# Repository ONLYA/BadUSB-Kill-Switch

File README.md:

# BadUSB Kill Switch
Methods to kill BadUSB:
* Software prevention
* Hardware prevention

## Software
This method detects unexpected HID devices input and block all keyboard inputs when that happens. For detail please have a look at [**Software section**](/Software).

## Hardware
This method detects whether the plugged USB device is HID device or not. For details please have a look at [**Hardware section**](/Hardware).

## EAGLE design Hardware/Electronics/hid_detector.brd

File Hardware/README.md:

# Hardware for BadUSB Kill Switch

This uses ATSAMD21E17D as the main chip for detection. This device is powered via the USB *Male* port to computer. When a USB device is plugged into the USB *Female* port on this device, it will start to detect whether the USB device is HID device or not.
* If the inserted USB device is NOT recognised as an HID, the **green** light will be lit and the data paths of it are switched on.
* If the inserted USB device is recognised as an HID, the **red** light will be lit while the **green** light is off and the datapaths of it will be switched off.

This device will keep detecting the USB protocol during the whole insertion in order to prevent possible remote or delayed attacks.

## Electronics [(Folder)](/Hardware/Electronics)
It contains the PCB and circuit design files of this device including the BOM file in csv format. Now it is completed.

## firmware [(Folder)](/Hardware/firmware)
It contains the firmware of the device so that it will work as described above. Now it is NOT completed.

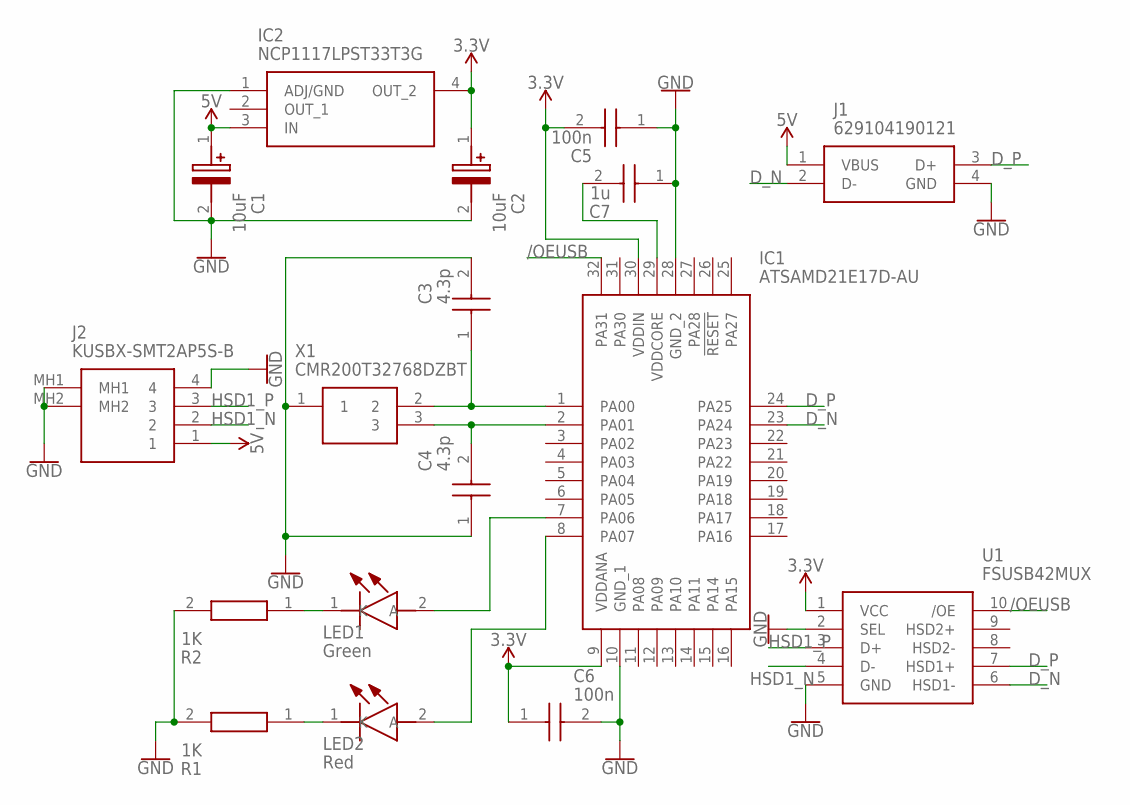
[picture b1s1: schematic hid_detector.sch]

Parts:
C1, C2: 10uF; CAPAE400X550N
C3, C4: 4.3p; CAPC0603X33N
C5, C6: 100n; CAPC1005X55N
C7: 1u; CAPC1005X55N
IC1: ATSAMD21E17D-AU; QFP80P900X900X120-32N
IC2: NCP1117LPST33T3G; SOT230P700X180-4N
J1: 629104190121
J2: KUSBX-SMT2AP5S-B; KUSBXSMT2AP5SB
LED1: Green; LEDC3215X130N
LED2: Red; LEDC1608X85N
R1, R2: 1K; RESC1005X40N
U1: FSUSB42MUX; SOP50P490X110-10N
X1: CMR200T32768DZBT; CMR200T

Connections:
3.3V: C2.1 (+), C5.2, C6.1, IC1.9 (VDDANA), IC1.30 (VDDIN), IC2.4 (OUT_2), U1.1 (VCC)
5V: C1.1 (+), IC2.3 (IN), J1.1 (VBUS), J2.1
/OEUSB: IC1.32 (PA31), U1.10 (/OE)
D_N: IC1.23 (PA24), J1.2 (D-), U1.6 (HSD1-)
D_P: IC1.24 (PA25), J1.3 (D+), U1.7 (HSD1+)
GND: C1.2 (-), C2.2 (-), C3.2, C4.1, C5.1, C6.2, C7.1, IC1.10 (GND_1), IC1.28 (GND_2), IC2.1 (ADJ/GND), J1.4 (GND), J2.4, J2.MH1, J2.MH2, R1.2, R2.2, U1.2 (SEL), U1.5 (GND), X1.1
HSD1_N: J2.2, U1.4 (D-)
HSD1_P: J2.3, U1.3 (D+)
unnamed: C3.1, IC1.1 (PA00), X1.2
unnamed: C4.2, IC1.2 (PA01), X1.3
unnamed: IC1.7 (PA06), LED1.2 (A)
unnamed: LED1.1 (K), R2.1
unnamed: C7.2, IC1.29 (VDDCORE)
unnamed: LED2.1 (K), R1.1
unnamed: IC1.8 (PA07), LED2.2 (A)

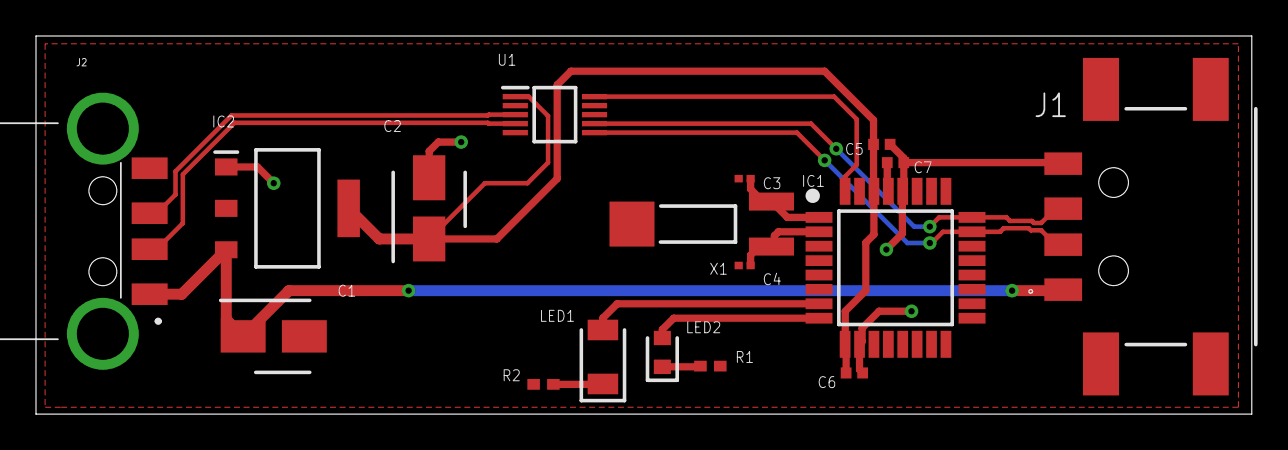
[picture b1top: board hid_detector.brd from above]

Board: 2 copper layers, 67.5 x 21.0 mm, 17 parts (0 on the bottom side), 15 nets.

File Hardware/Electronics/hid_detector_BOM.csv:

"Part";"Value";"Device";"Package";"Description";"DESCRIPTION";"HEIGHT";"MANUFACTURER_NAME";"MANUFACTURER_PART_NUMBER";"MOUSER_PART_NUMBER";"MOUSER_PRICE-STOCK";
"C1";"10uF";"865080440002";"CAPAE400X550N";"Wurth Elektronik 10uF 25 V dc Aluminium Electrolytic Capacitor, WCAP-ASLI Series 2000h 4 (Dia.) x 5.35mm";"Wurth Elektronik 10uF 25 V dc Aluminium Electrolytic Capacitor, WCAP-ASLI Series 2000h 4 (Dia.) x 5.35mm";"5.5mm";"Wurth Elektronik";"865080440002";"710-865080440002";"https://www.mouser.co.uk/ProductDetail/Wurth-Elektronik/8650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";
"C2";"10uF";"865080440002";"CAPAE400X550N";"Wurth Elektronik 10uF 25 V dc Aluminium Electrolytic Capacitor, WCAP-ASLI Series 2000h 4 (Dia.) x 5.35mm";"Wurth Elektronik 10uF 25 V dc Aluminium Electrolytic Capacitor, WCAP-ASLI Series 2000h 4 (Dia.) x 5.35mm";"5.5mm";"Wurth Elektronik";"865080440002";"710-865080440002";"https://www.mouser.co.uk/ProductDetail/Wurth-Elektronik/8650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";
"C3";"4.3p";"GRM0335C1E4R3WA01D";"CAPC0603X33N";"Chip Capacitor value 4R3";"Chip Capacitor value 4R3";"0.33mm";"Murata Electronics";"GRM0335C1E4R3WA01D";"";"";
"C4";"4.3p";"GRM0335C1E4R3WA01D";"CAPC0603X33N";"Chip Capacitor value 4R3";"Chip Capacitor value 4R3";"0.33mm";"Murata Electronics";"GRM0335C1E4R3WA01D";"";"";
"C5";"100n";"EMF105B7104MVHF";"CAPC1005X55N";"Multilayer Ceramic Capacitors MLCC - SMD/SMT 0402 16V 0.1uF 20% AEC-Q200";"Multilayer Ceramic Capacitors MLCC - SMD/SMT 0402 16V 0.1uF 20% AEC-Q200";"0.55mm";"TAIYO YUDEN";"EMF105B7104MVHF";"963-EMF105B7104MVHF";"https://www.mouser.co.uk/ProductDetail/Taiyo-Yuden/EMF105B71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";
"C6";"100n";"EMF105B7104MVHF";"CAPC1005X55N";"Multilayer Ceramic Capacitors MLCC - SMD/SMT 0402 16V 0.1uF 20% AEC-Q200";"Multilayer Ceramic Capacitors MLCC - SMD/SMT 0402 16V 0.1uF 20% AEC-Q200";"0.55mm";"TAIYO YUDEN";"EMF105B7104MVHF";"963-EMF105B7104MVHF";"https://www.mouser.co.uk/ProductDetail/Taiyo-Yuden/EMF105B71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";
"C7";"1u";"EMK105BJ105MVHF";"CAPC1005X55N";"TAIYO YUDEN - EMK105BJ105MVHF - CAPACITOR, MLCC, 0402, 16V ,X5R,Q200 02AH5330";"TAIYO YUDEN - EMK105BJ105MVHF - CAPACITOR, MLCC, 0402, 16V ,X5R,Q200 02AH5330";"0.55mm";"TAIYO YUDEN";"EMK105BJ105MVHF";"963-EMK105BJ105MVHF";"https://www.mouser.co.uk/ProductDetail/Taiyo-Yuden/EMK105BJ1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";
"IC1";"ATSAMD21E17D-AU";"ATSAMD21E17D-AU";"QFP80P900X900X120-32N";"ARM Microcontrollers - MCU 32TQFP IND TEMP, GREEN,1.6-3.6V,48MHz";"ARM Microcontrollers - MCU 32TQFP IND TEMP, GREEN,1.6-3.6V,48MHz";"1.2mm";"Microchip";"ATSAMD21E17D-AU";"556-ATSAMD21E17D-AU";"https://www.mouser.co.uk/ProductDetail/Microchip-Technology/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";
"IC2";"NCP1117LPST33T3G";"NCP1117LPST33T3G";"SOT230P700X180-4N";"Source:  Datasheet";"";"1.8mm";"ON Semiconductor";"NCP1117LPST33T3G";"863-NCP1117LPST33T3G";"https://www.mouser.co.uk/ProductDetail/ON-Semiconductor/NCP1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";
"J1";"629104190121";"629104190121";"629104190121";"WURTH ELEKTRONIK - 629104190121 - CONN, USB 2 TYPE A, RCPT, 4POS, SMT";"WURTH ELEKTRONIK - 629104190121 - CONN, USB 2 TYPE A, RCPT, 4POS, SMT";"mm";"Wurth Elektronik";"629104190121";"710-629104190121";"https://www.mouser.co.uk/ProductDetail/Wurth-Elektronik/6291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";
"J2";"KUSBX-SMT2AP5S-B";"KUSBX-SMT2AP5S-B";"KUSBXSMT2AP5SB";"USB Connectors A TYPE SMT BLK PLUG 1.35mm POSTS SHIELD";"USB Connectors A TYPE SMT BLK PLUG 1.35mm POSTS SHIELD";"4.75mm";"Kycon";"KUSBX-SMT2AP5S-B";"806-KUSBXSMT2AP5SB";"https://www.mouser.co.uk/ProductDetail/Kycon/KUSBX-SMT2AP5S-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";
"LED1";"Green";"CMD15-21VGD_TR8";"LEDC3215X130N";"VCC CMD15-21VGD/TR8, CMD15-21 Series Clear LED, 570 nm,, Rectangle Lens";"VCC CMD15-21VGD/TR8, CMD15-21 Series Clear LED, 570 nm,, Rectangle Lens";"1.3mm";"Visual Communications Company";"CMD15-21VGD/TR8";"606-CMD15-21VGD/TR8";"https://www.mouser.com/Search/Refine.aspx?Keyword=606-CMD15-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";
"LED2";"Red";"APT1608EC";"LEDC1608X85N";"Standard LEDs - SMD HI EFF RED WTR CLR";"Standard LEDs - SMD HI EFF RED WTR CLR";"0.85mm";"Kingbright";"APT1608EC";"604-APT1608EC";"https://www.mouser.co.uk/ProductDetail/Kingbright/APT1608EC?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";
"R1";"1K";"RK73H1ETTP1001F";"RESC1005X40N";"Thick Film Resistors - SMD 1/16watts 1Kohms 1%";"Thick Film Resistors - SMD 1/16watts 1Kohms 1%";"0.4mm";"KOA Speer";"RK73H1ETTP1001F";"660-RK73H1ETTP1001F";"https://www.mouser.com/Search/Refine.aspx?Keyword=660-RK73H1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";
"R2";"1K";"RK73H1ETTP1001F";"RESC1005X40N";"Thick Film Resistors - SMD 1/16watts 1Kohms 1%";"Thick Film Resistors - SMD 1/16watts 1Kohms 1%";"0.4mm";"KOA Speer";"RK73H1ETTP1001F";"660-RK73H1ETTP1001F";"https://www.mouser.com/Search/Refine.aspx?Keyword=660-RK73H1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";
"U1";"FSUSB42MUX";"FSUSB42MUX";"SOP50P490X110-10N";"ON SEMICONDUCTOR - FSUSB42MUX - USB SWITCH, DUAL, DPDT, MSOP-10";"ON SEMICONDUCTOR - FSUSB42MUX - USB SWITCH, DUAL, DPDT, MSOP-10";"1.1mm";"ON Semiconductor";"FSUSB42MUX";"512-FSUSB42MUX";"https://www.mouser.co.uk/ProductDetail/ON-Semiconductor-Fair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";
"X1";"CMR200T32768DZBT";"CMR200T32768DZBT";"CMR200T";"Crystals 32.768 KHz 6 pF REFLOWABLE SMD";"Crystals 32.768 KHz 6 pF REFLOWABLE SMD";"mm";"Citizen Finetech Miyota";"CMR200T32768DZBT";"695-CMR200T32768DZBT";"https://www.mouser.co.uk/ProductDetail/Citizen-FineDevice/CM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";

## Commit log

2020-08-16 Init
2020-08-17 READMEs
2020-08-19 README updates
2020-08-20 Software additions
2020-08-22 Software Part Update
2020-08-23 Windows Version
2020-08-29 Hardware section. Circuits finished. Firmware not complete.
    PCB&Circuits complete. Firmware awaits.
2020-09-07 Hardware Electronics & Firmware
2020-11-14 Part
2021-12-07 Hardware v2
2021-12-07 Create LICENSE

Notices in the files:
parts and their libraries:
SparkFun-PowerSymbols: Licensing: Creative Commons ShareAlike 4.0 International - https://creativecommons.org/licenses/by-sa/4.0
